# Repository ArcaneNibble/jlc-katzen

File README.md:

# Just testing JLCPCB turn-key assembly with a blinky toy

## ERRATA

* USB D+/D- are flipped!
* wrong crystal load capacitors

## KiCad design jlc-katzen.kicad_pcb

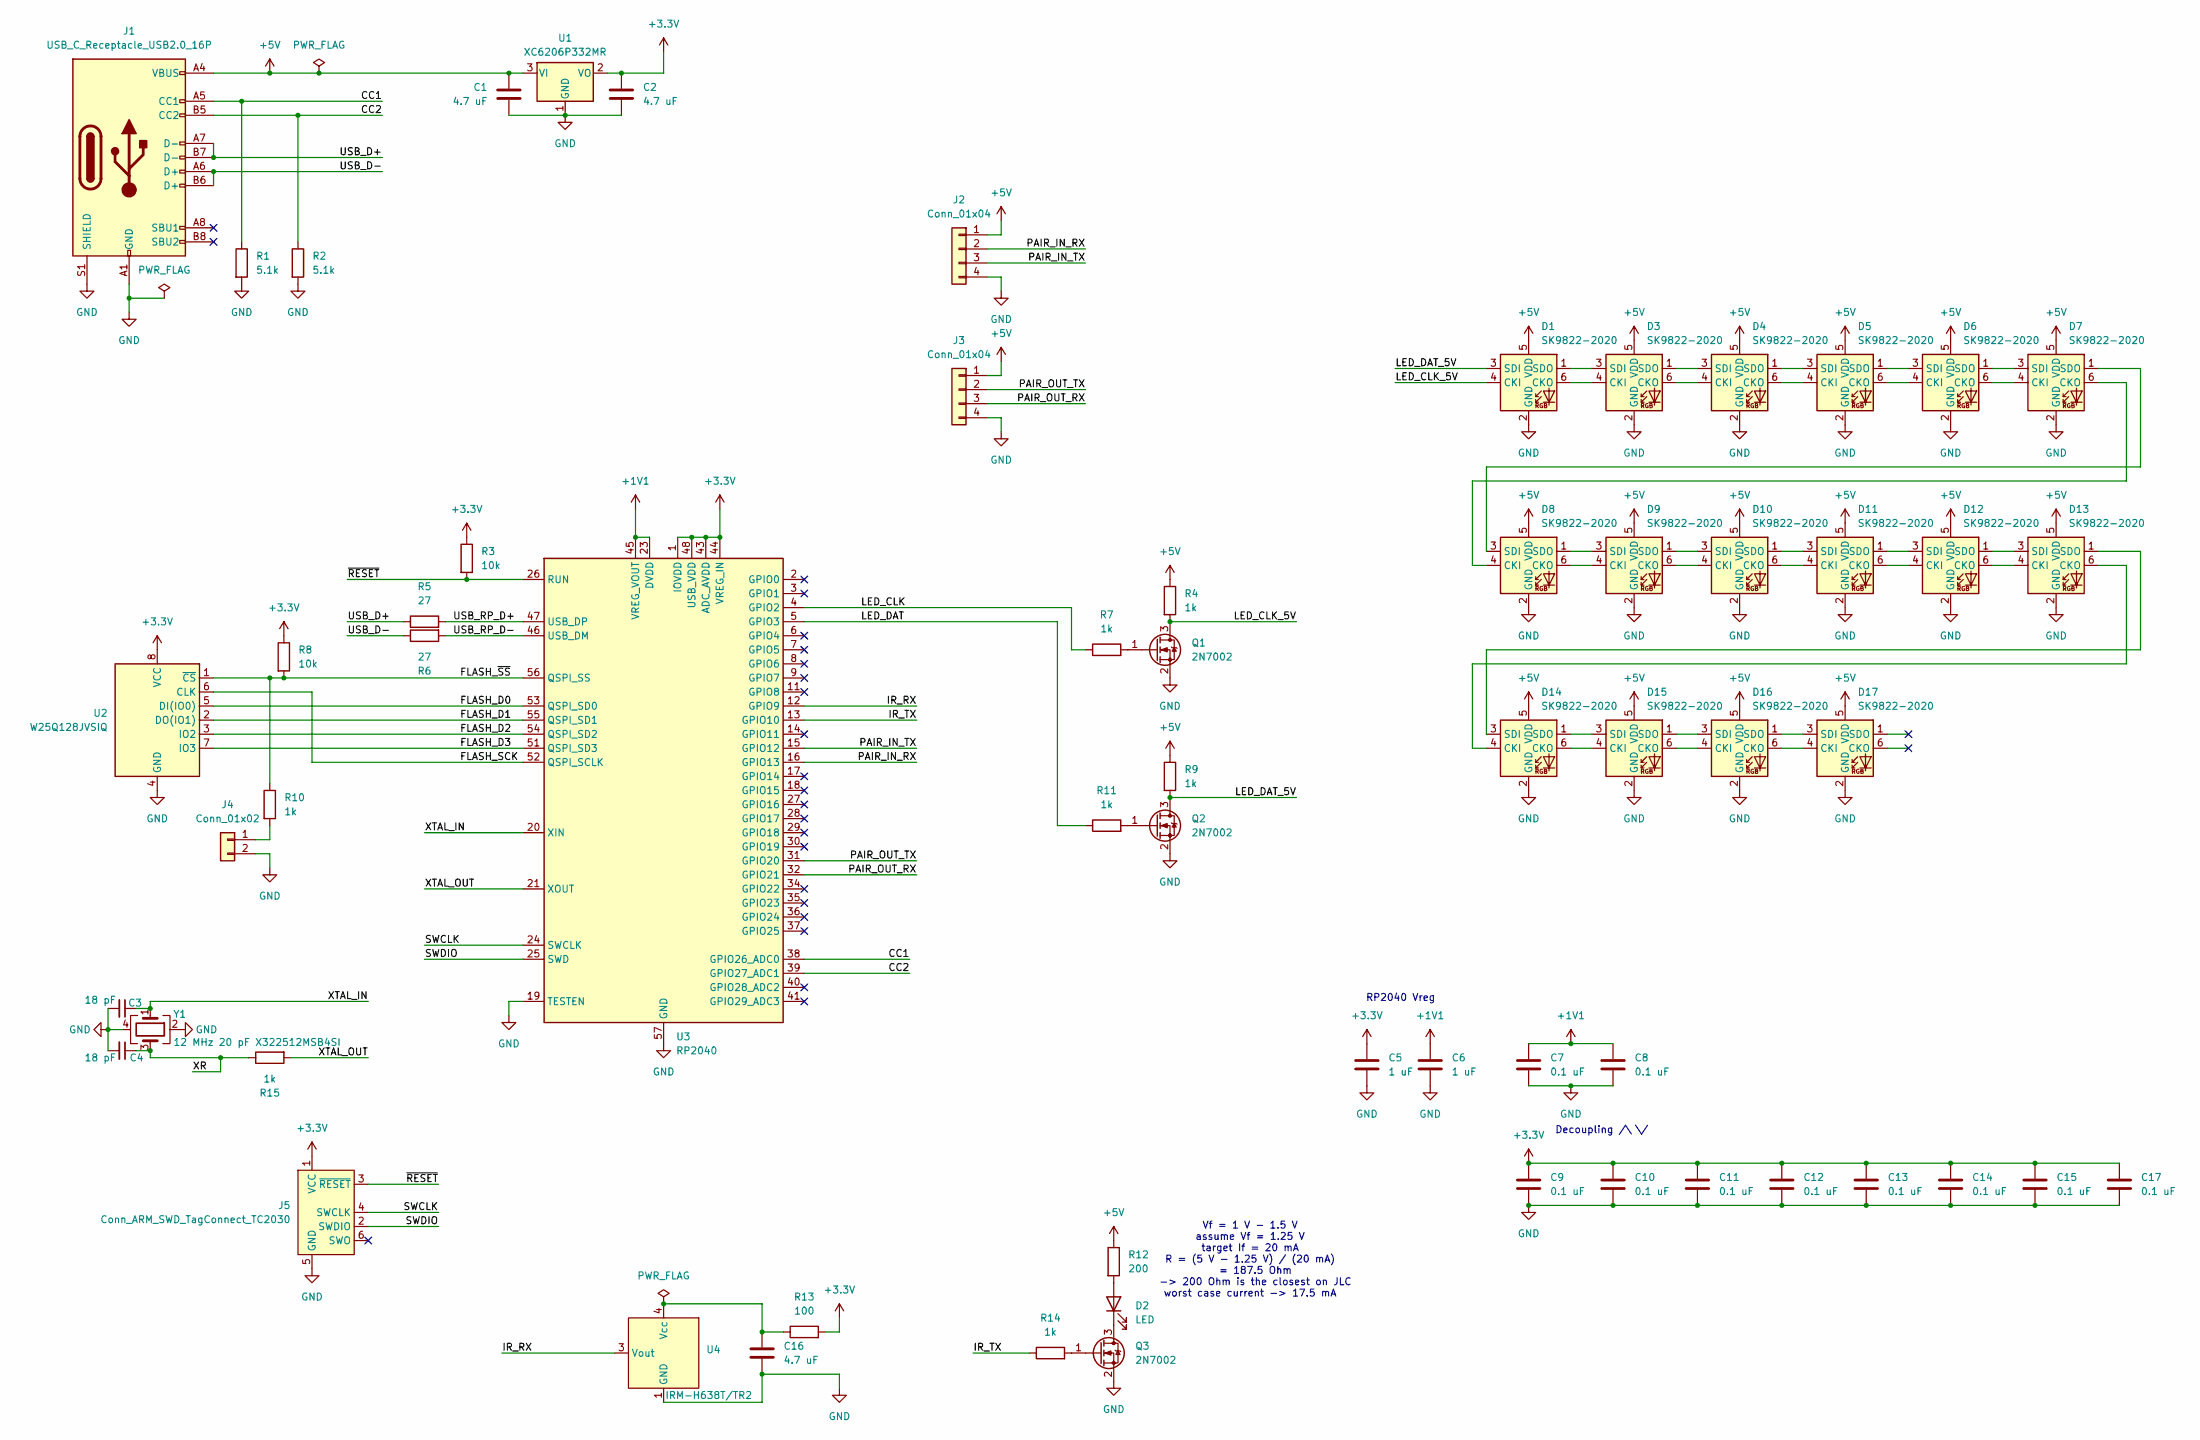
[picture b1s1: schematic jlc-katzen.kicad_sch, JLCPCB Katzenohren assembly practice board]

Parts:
C1, C2: 4.7 uF; C_0805_2012Metric; LCSC C1779
C3, C4: 18 pF; C_0402_1005Metric; LCSC C1549
C5, C6: 1 uF; C_0603_1608Metric; LCSC C15849
C7, C8, C9, C10, C11, C12, C13, C14, C15, C17: 0.1 uF; C_0402_1005Metric; LCSC C1525
C16: 4.7 uF; C_0402_1005Metric; LCSC C23733
D1, D3, D4, D5, D6, D7, D8, D9, D10, D11, D12, D13, D14, D15, D16, D17: SK9822-2020; LED-SK9822-2020; LCSC C2909059
D2: LED; LED_0805_2012Metric; LCSC C131250
J1: USB_C_Receptacle_USB2.0_16P; USB_C_Receptacle_GCT_USB4105-xx-A_16P_TopMnt_Horizontal; LCSC C2765186
J2, J3: Conn_01x04; PinHeader_1x04_P1.27mm_Vertical
J4: Conn_01x02; PinHeader_1x02_P1.27mm_Vertical
J5: Conn_ARM_SWD_TagConnect_TC2030; Tag-Connect_TC2030-IDC-FP_2x03_P1.27mm_Vertical
Q1, Q2, Q3: 2N7002; SOT-23; LCSC C7420321
R1, R2: 5.1k; R_0402_1005Metric; LCSC C25905
R3, R8: 10k; R_0402_1005Metric; LCSC C25744
R4, R7, R9, R10, R11, R14, R15: 1k; R_0402_1005Metric; LCSC C11702
R5, R6: 27; R_0603_1608Metric; LCSC C25190
R12: 200; R_0603_1608Metric; LCSC C8218
R13: 100; R_0402_1005Metric; LCSC C25076
U1: XC6206P332MR; SOT-23-3; LCSC C5446
U2: W25Q128JVSIQ; SOIC-8_5.23x5.23mm_P1.27mm; LCSC C97521
U3: RP2040; QFN-56-1EP_7x7mm_P0.4mm_EP3.2x3.2mm; LCSC C2040
U4: IRM-H638T/TR2; IRM-H6XXT; LCSC C91447
Y1: 12 MHz 20 pF X322512MSB4SI; Crystal_SMD_3225-4Pin_3.2x2.5mm; LCSC C9002

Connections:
+1V1: C6.1, C7.1, C8.1, U3.23 (DVDD), U3.45 (VREG_VOUT), U3.50 (DVDD)
+3.3V: C2.1, C5.1, C9.1, C10.1, C11.1, C12.1, C13.1, C14.1, C15.1, C17.1, J5.1 (VCC), R3.1, R8.1, R13.2, U1.2 (VO), U2.8 (VCC), U3.1 (IOVDD), U3.10 (IOVDD), U3.22 (IOVDD), U3.33 (IOVDD), U3.42 (IOVDD), U3.43 (ADC_AVDD), U3.44 (VREG_IN), U3.48 (USB_VDD), U3.49 (IOVDD)
+5V: C1.1, D1.5 (VDD), D3.5 (VDD), D4.5 (VDD), D5.5 (VDD), D6.5 (VDD), D7.5 (VDD), D8.5 (VDD), D9.5 (VDD), D10.5 (VDD), D11.5 (VDD), D12.5 (VDD), D13.5 (VDD), D14.5 (VDD), D15.5 (VDD), D16.5 (VDD), D17.5 (VDD), J1.A4 (VBUS), J1.A9 (VBUS), J1.B4 (VBUS), J1.B9 (VBUS), J2.1, J3.1, R4.1, R9.1, R12.1, U1.3 (VI)
/CC1: J1.A5 (CC1), R1.1, U3.38 (GPIO26_ADC0)
/CC2: J1.B5 (CC2), R2.1, U3.39 (GPIO27_ADC1)
/FLASH_D0: U2.5 (DI(IO0)), U3.53 (QSPI_SD0)
/FLASH_D1: U2.2 (DO(IO1)), U3.55 (QSPI_SD1)
/FLASH_D2: U2.3 (IO2), U3.54 (QSPI_SD2)
/FLASH_D3: U2.7 (IO3), U3.51 (QSPI_SD3)
/FLASH_SCK: U2.6 (CLK), U3.52 (QSPI_SCLK)
/FLASH_~SS: R8.2, R10.1, U2.1 (~CS), U3.56 (QSPI_SS)
/IR_RX: U3.12 (GPIO9), U4.3 (Vout)
/IR_TX: R14.1, U3.13 (GPIO10)
/LED_CLK: R7.1, U3.4 (GPIO2)
/LED_CLK_5V: D1.4 (CKI), Q1.3 (D), R4.2
/LED_DAT: R11.1, U3.5 (GPIO3)
/LED_DAT_5V: D1.3 (SDI), Q2.3 (D), R9.2
/PAIR_IN_RX: J2.2, U3.16 (GPIO13)
/PAIR_IN_TX: J2.3, U3.15 (GPIO12)
/PAIR_OUT_RX: J3.3, U3.32 (GPIO21)
/PAIR_OUT_TX: J3.2, U3.31 (GPIO20)
/SWCLK: J5.4 (SWCLK), U3.24 (SWCLK)
/SWDIO: J5.2 (SWDIO), U3.25 (SWD)
/USB_D+: J1.A7 (D-), J1.B7 (D-), R5.1
/USB_D-: J1.A6 (D+), J1.B6 (D+), R6.1
/USB_RP_D+: R5.2, U3.47 (USB_DP)
/USB_RP_D-: R6.2, U3.46 (USB_DM)
/XR: C4.1, R15.1, Y1.3
/XTAL_IN: C3.1, U3.20 (XIN), Y1.1
/XTAL_OUT: R15.2, U3.21 (XOUT)
/~RESET: J5.3 (~RESET), R3.2, U3.26 (RUN)
GND: C1.2, C2.2, C3.2, C4.2, C5.2, C6.2, C7.2, C8.2, C9.2, C10.2, C11.2, C12.2, C13.2, C14.2, C15.2, C16.2, C17.2, D1.2 (GND), D3.2 (GND), D4.2 (GND), D5.2 (GND), D6.2 (GND), D7.2 (GND), D8.2 (GND), D9.2 (GND), D10.2 (GND), D11.2 (GND), D12.2 (GND), D13.2 (GND), D14.2 (GND), D15.2 (GND), D16.2 (GND), D17.2 (GND), J1.A1 (GND), J1.A12 (GND), J1.B1 (GND), J1.B12 (GND), J1.S1 (SHIELD), J2.4, J3.4, J4.2, J5.5 (GND), Q1.2 (S), Q2.2 (S), Q3.2 (S), R1.2, R2.2, U1.1 (GND), U2.4 (GND), U3.19 (TESTEN), U3.57 (GND), U4.1 (GND), U4.2 (GND), Y1.2, Y1.4
unnamed: D1.6 (CKO), D3.4 (CKI)
unnamed: D1.1 (SDO), D3.3 (SDI)
unnamed: D2.2 (A), R12.2
unnamed: D2.1 (K), Q3.3 (D)
unnamed: D3.6 (CKO), D4.4 (CKI)
unnamed: D3.1 (SDO), D4.3 (SDI)
unnamed: D4.6 (CKO), D5.4 (CKI)
unnamed: D4.1 (SDO), D5.3 (SDI)
unnamed: D5.6 (CKO), D6.4 (CKI)
unnamed: D5.1 (SDO), D6.3 (SDI)
unnamed: D6.6 (CKO), D7.4 (CKI)
unnamed: D6.1 (SDO), D7.3 (SDI)
unnamed: D7.6 (CKO), D8.4 (CKI)
unnamed: D7.1 (SDO), D8.3 (SDI)
unnamed: D8.6 (CKO), D9.4 (CKI)
unnamed: D8.1 (SDO), D9.3 (SDI)
unnamed: D9.6 (CKO), D10.4 (CKI)
unnamed: D10.6 (CKO), D11.4 (CKI)
unnamed: D9.1 (SDO), D10.3 (SDI)
unnamed: D10.1 (SDO), D11.3 (SDI)
unnamed: D11.6 (CKO), D12.4 (CKI)
unnamed: D11.1 (SDO), D12.3 (SDI)
unnamed: D12.6 (CKO), D13.4 (CKI)
unnamed: D12.1 (SDO), D13.3 (SDI)
unnamed: D13.6 (CKO), D14.4 (CKI)
unnamed: D13.1 (SDO), D14.3 (SDI)
unnamed: D14.6 (CKO), D15.4 (CKI)
unnamed: D14.1 (SDO), D15.3 (SDI)
unnamed: D15.6 (CKO), D16.4 (CKI)
unnamed: D15.1 (SDO), D16.3 (SDI)
unnamed: D16.6 (CKO), D17.4 (CKI)
unnamed: D16.1 (SDO), D17.3 (SDI)
unnamed: J4.1, R10.2
unnamed: Q1.1 (G), R7.2
unnamed: Q2.1 (G), R11.2
unnamed: Q3.1 (G), R14.2
unnamed: C16.1, R13.1, U4.4 (Vcc)

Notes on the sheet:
Vf = 1 V - 1.5 V assume Vf = 1.25 V target If = 20 mA R = (5 V - 1.25 V) / (20 mA) = 187.5 Ohm -> 200 Ohm is the closest on JLC worst case current -> 17.5 mA
RP2040 Vreg
Decoupling /\ \/

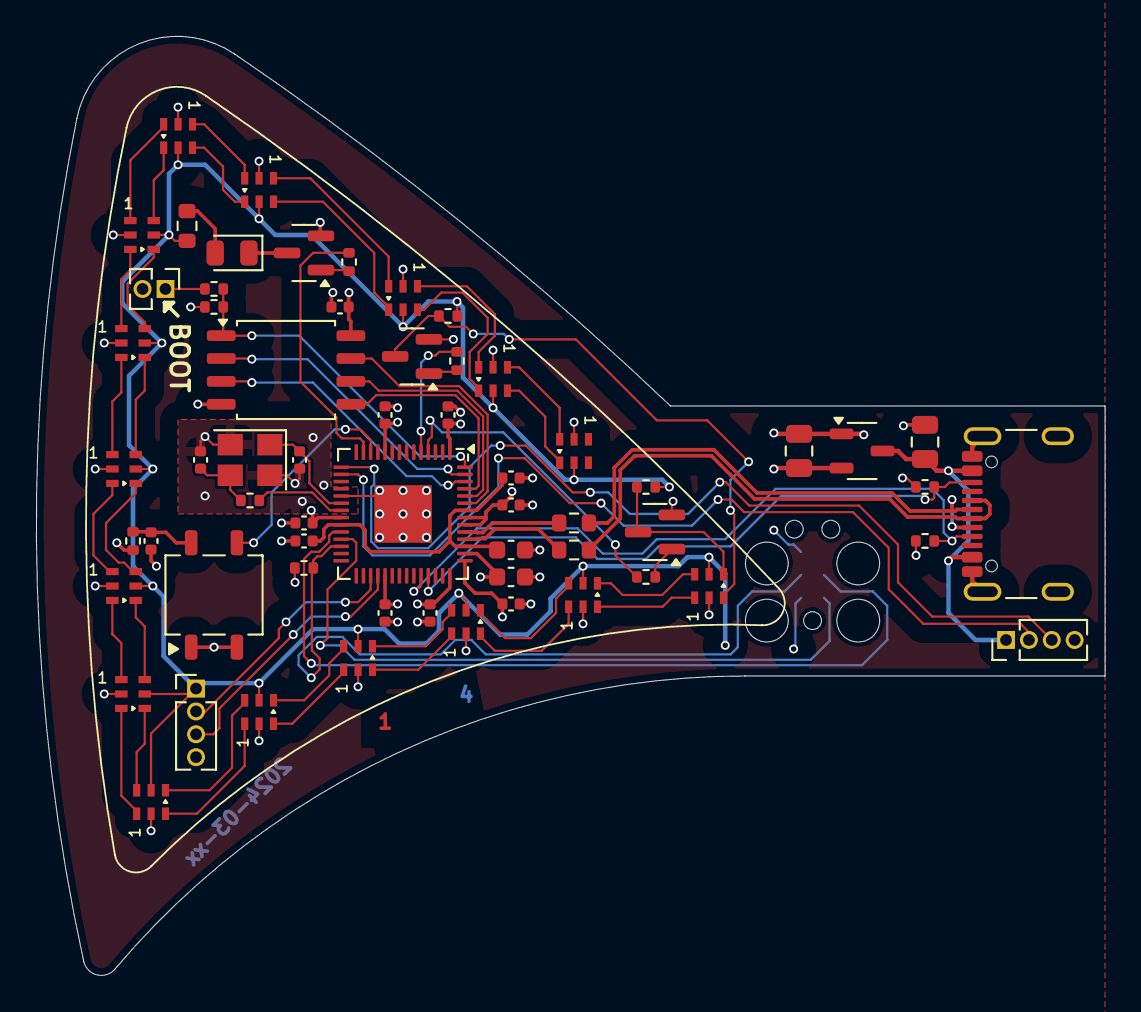
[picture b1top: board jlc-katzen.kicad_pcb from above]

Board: 4 copper layers, 59.4 x 52.2 mm, 62 parts (1 on the bottom side), 69 nets.

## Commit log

2024-03-15 copy-paste sk9822 part from paranoids badge
2024-03-15 throw on basic parts
2024-03-15 draft sch
2024-03-15 ir rx footprint
2024-03-15 footprints, part numbers
2024-03-15 throw parts on a pcb of some kind
2024-03-15 useless twiddles
2024-03-15 fix crystal
2024-03-15 fix sk9822 footprint
2024-03-15 name some nets
2024-03-15 hopefully fit this many leds
2024-03-16 rough route
2024-03-16 all nets connected
2024-03-16 mark unused
2024-03-16 clean traces, hide refdes on silk
2024-03-16 clean silk, tweak traces more
2024-03-16 more silk, tweaks
2024-03-16 move ir tx/rx to separate pwm blocks
    (even if we use PIO instead)
2024-03-16 make labels on sch attach to ends of wires
2024-03-16 fix sch metadata
2024-03-17 fix pcb metadata
2024-03-17 add thieving
2024-03-17 plot A1
2024-03-17 thieving coverage not sufficient -> fill
2024-03-17 tweak fills
2024-09-04 xxx changes to files
2024-09-04 Add README
2024-09-04 add other error
